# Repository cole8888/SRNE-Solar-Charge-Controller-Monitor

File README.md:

# SRNE-Solar-Charge-Controller-Monitor

Read data from SRNE solar charge controllers via modbus over RS232.

This repository contains several example programs for reading data from SRNE solar charge controllers using Raspberry Pi, ESP32, ESP8266 and Arduino Nano / Uno.

Based on the modbus manuals, this should also work with some Renogy controllers, but I don't have one to test with. Also, verify the wiring is compatible with your controller.

<hr>

## Example Setups:

Here are some example programs to get started. If you follow the setup instructions in the readme files of each directory, you should be able to talk to your controller. If you are just getting started, don't use the MQTT ones.

### [Raspberry Pi](./RaspberryPi-Examples/)

### [ESP32](./ESP32-Examples/)

### [ESP8266](./ESP8266-Examples/)

### [Arduino Nano / Uno](./Arduino-Example/)

<hr>

## Web-Interface and MQTT

I've included an [example web interface](./Web-Interface-Example/) you can use in combination with the MQTT-enabled example programs. To use it, you will need to setup an MQTT broker such as [Mosquitto](https://github.com/eclipse/mosquitto) or use a cloud broker. You will also need to set all the appropriate settings in the chosen program and the [index.js](./Web-Interface-Example/index.js) file.

I also included my [custom web interface](./My-Current-Setup/Web-Interface/) which I am using for my setup. It has the ability to read data from and control smart plugs flashed with Tasmota.

<hr>

## My Current Setup:

The setup I use is a customized version of the ESP32 Example, I also designed a custom PCB. Have a look at [My-Current-Setup](./My-Current-Setup) if you want some inspiration for your own setup!

<hr>

## Troubleshooting:

If you notice lots of timeouts, or other errors, try some these steps before creating an issue:

- Try a different power supply and USB cable. My ML2440 does not respond when I use one of my USB power bricks, but it does with another.
- Try increasing the modbus timeout value.
- Try using a shorter cables and moving them away from interference.
- Verify you are using straight cables and not ones that reverse from one end to the other.
- Try using HardwareSerial instead of SoftwareSerial. I've found HardwareSerial is more reliable, configure the program to use it if you are having problems.

<b>If these don't help or if you need clarification, feel free to create an issue and I'll see what I can do!</b>

<hr>

## Other notes:

- I've included the [SRNE modbus manual](./SRNE-MODBUS.pdf) if you want to have a look at it. My examples read all the registers I think are important, but there are lots of other registers which I haven't touched. Be careful, some of them can be written to!

- The Python version was originally based on: http://vcsco.com/uncategorized/renogy-rover-monitoring-with-the-raspberry-pi/

- The Web-Interface was originally based on: https://github.com/fabaff/mqtt-panel

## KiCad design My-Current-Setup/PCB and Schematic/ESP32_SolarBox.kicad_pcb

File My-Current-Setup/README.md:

# My-Current-Setup

This is the setup I currently use. Feel free to use it for inspiration!

This version isn't intended to be plug and play like the other examples as it is specific to my needs.

## Layout

I have 3 solar charge controllers, one for the front, side, and back arrays. They feed into the ESP32 which collects the data and publishes it to an MQTT server that clients (such as the web-ui) can connect to.

I also have an ESP8266 with an LCD attached that subscribes to the MQTT feed to display some data in a convenient location around the house.

## Libraries

The libraries this project uses are:

- https://github.com/4-20ma/ModbusMaster
- https://github.com/bblanchon/ArduinoJson
- https://github.com/knolleary/pubsubclient
- https://github.com/plerup/espsoftwareserial/ (Optional, needed for >2 controllers)
- https://github.com/ayushsharma82/AsyncElegantOTA (Optional, Over the air updates)
- https://github.com/ayushsharma82/WebSerial (Optional, Over the air debugging)
- https://github.com/me-no-dev/ESPAsyncWebServer/ (Dependency of OTA and WebSerial)
- https://github.com/me-no-dev/AsyncTCP/ (Dependency of OTA and WebSerial)
- https://github.com/fdebrabander/Arduino-LiquidCrystal-I2C-library (Optional, for receiver)

## Hardware

### PCB

I designed a custom PCB for this, have a look at the [PCB files and schematic](./PCB%20and%20Schematic/).

Each PCB can handle up to 6 charge controllers at once!

NOTE: If you do plan to use my PCB, make sure you verify the footprint of the ESP32 you plan to use. The ones I have are a bit narrower than most, so you may need to adjust the footprint.

### Components:

This list is for a fully populated PCB, you may not need everything here, see schematic for details.

- 1 x [ESP32 DevKit Narrow](https://www.amazon.ca/gp/product/B07QCP2451/) (Unless you adjusted the PCB footprint yourself)
- 3 x [MAX3232](https://www.digikey.ca/en/products/detail/analog-devices-inc-maxim-integrated/MAX3232EEPE/1512691) (Or equivalent)
- 3 x [10uF Capacitor](https://www.digikey.ca/en/products/detail/nichicon/ULD2A100MED1TD/7365013)
- 9 x [0.47uF Capacitor](https://www.digikey.ca/en/products/detail/tdk-corporation/FG28X7R1H474KRT06/5803214)
- 3 x [0.1uF Capacitor](https://www.digikey.ca/en/products/detail/vishay-beyschlag-draloric-bc-components/K104K15X7RF5TL2/286538)
- 6 x [1kOhm Resistor](https://www.digikey.ca/en/products/detail/stackpole-electronics-inc/CF14JT1K00/1741314)
- 6 x [6P6C Jack](https://www.digikey.ca/en/products/detail/amphenol-cs-commercial-products/RJE031660110/4889694)
- 6 x [6P6C Straight Cable](https://www.digikey.ca/en/products/detail/assmann-wsw-components/AT-S-26-6-6-B-7-R/1972588)
- 2 x [1000uF Capacitor](https://www.digikey.ca/en/products/detail/rubycon/35ZLH1000MEFC12-5X20/3564067) (Recommended)
- 2 x [19 Position Female Header](https://www.digikey.ca/en/products/detail/sullins-connector-solutions/PPTC191LFBN-RC/810157) (Recommended, for ESP32)
- 3 x [16 Pin Dip Socket](https://www.digikey.ca/en/products/detail/amphenol-cs-fci/DILB16P-223TLF/4292068) (Recommended, for MAX3232)
- 1 x [3 position screw terminal](https://www.digikey.ca/en/products/detail/phoenix-contact/1984620/950850) (Optional)

## Web Interface

This is a customized version of the [example web interface](../Web-Interface-Example/). It has a different layout since I needed to display data from 3 charge controllers while also having smart plug controls.

<hr>

- The Web interface was originally based on https://github.com/fabaff/mqtt-panel
- Server icon in diagram is from [Roundicons](https://www.flaticon.com/free-icons/server).

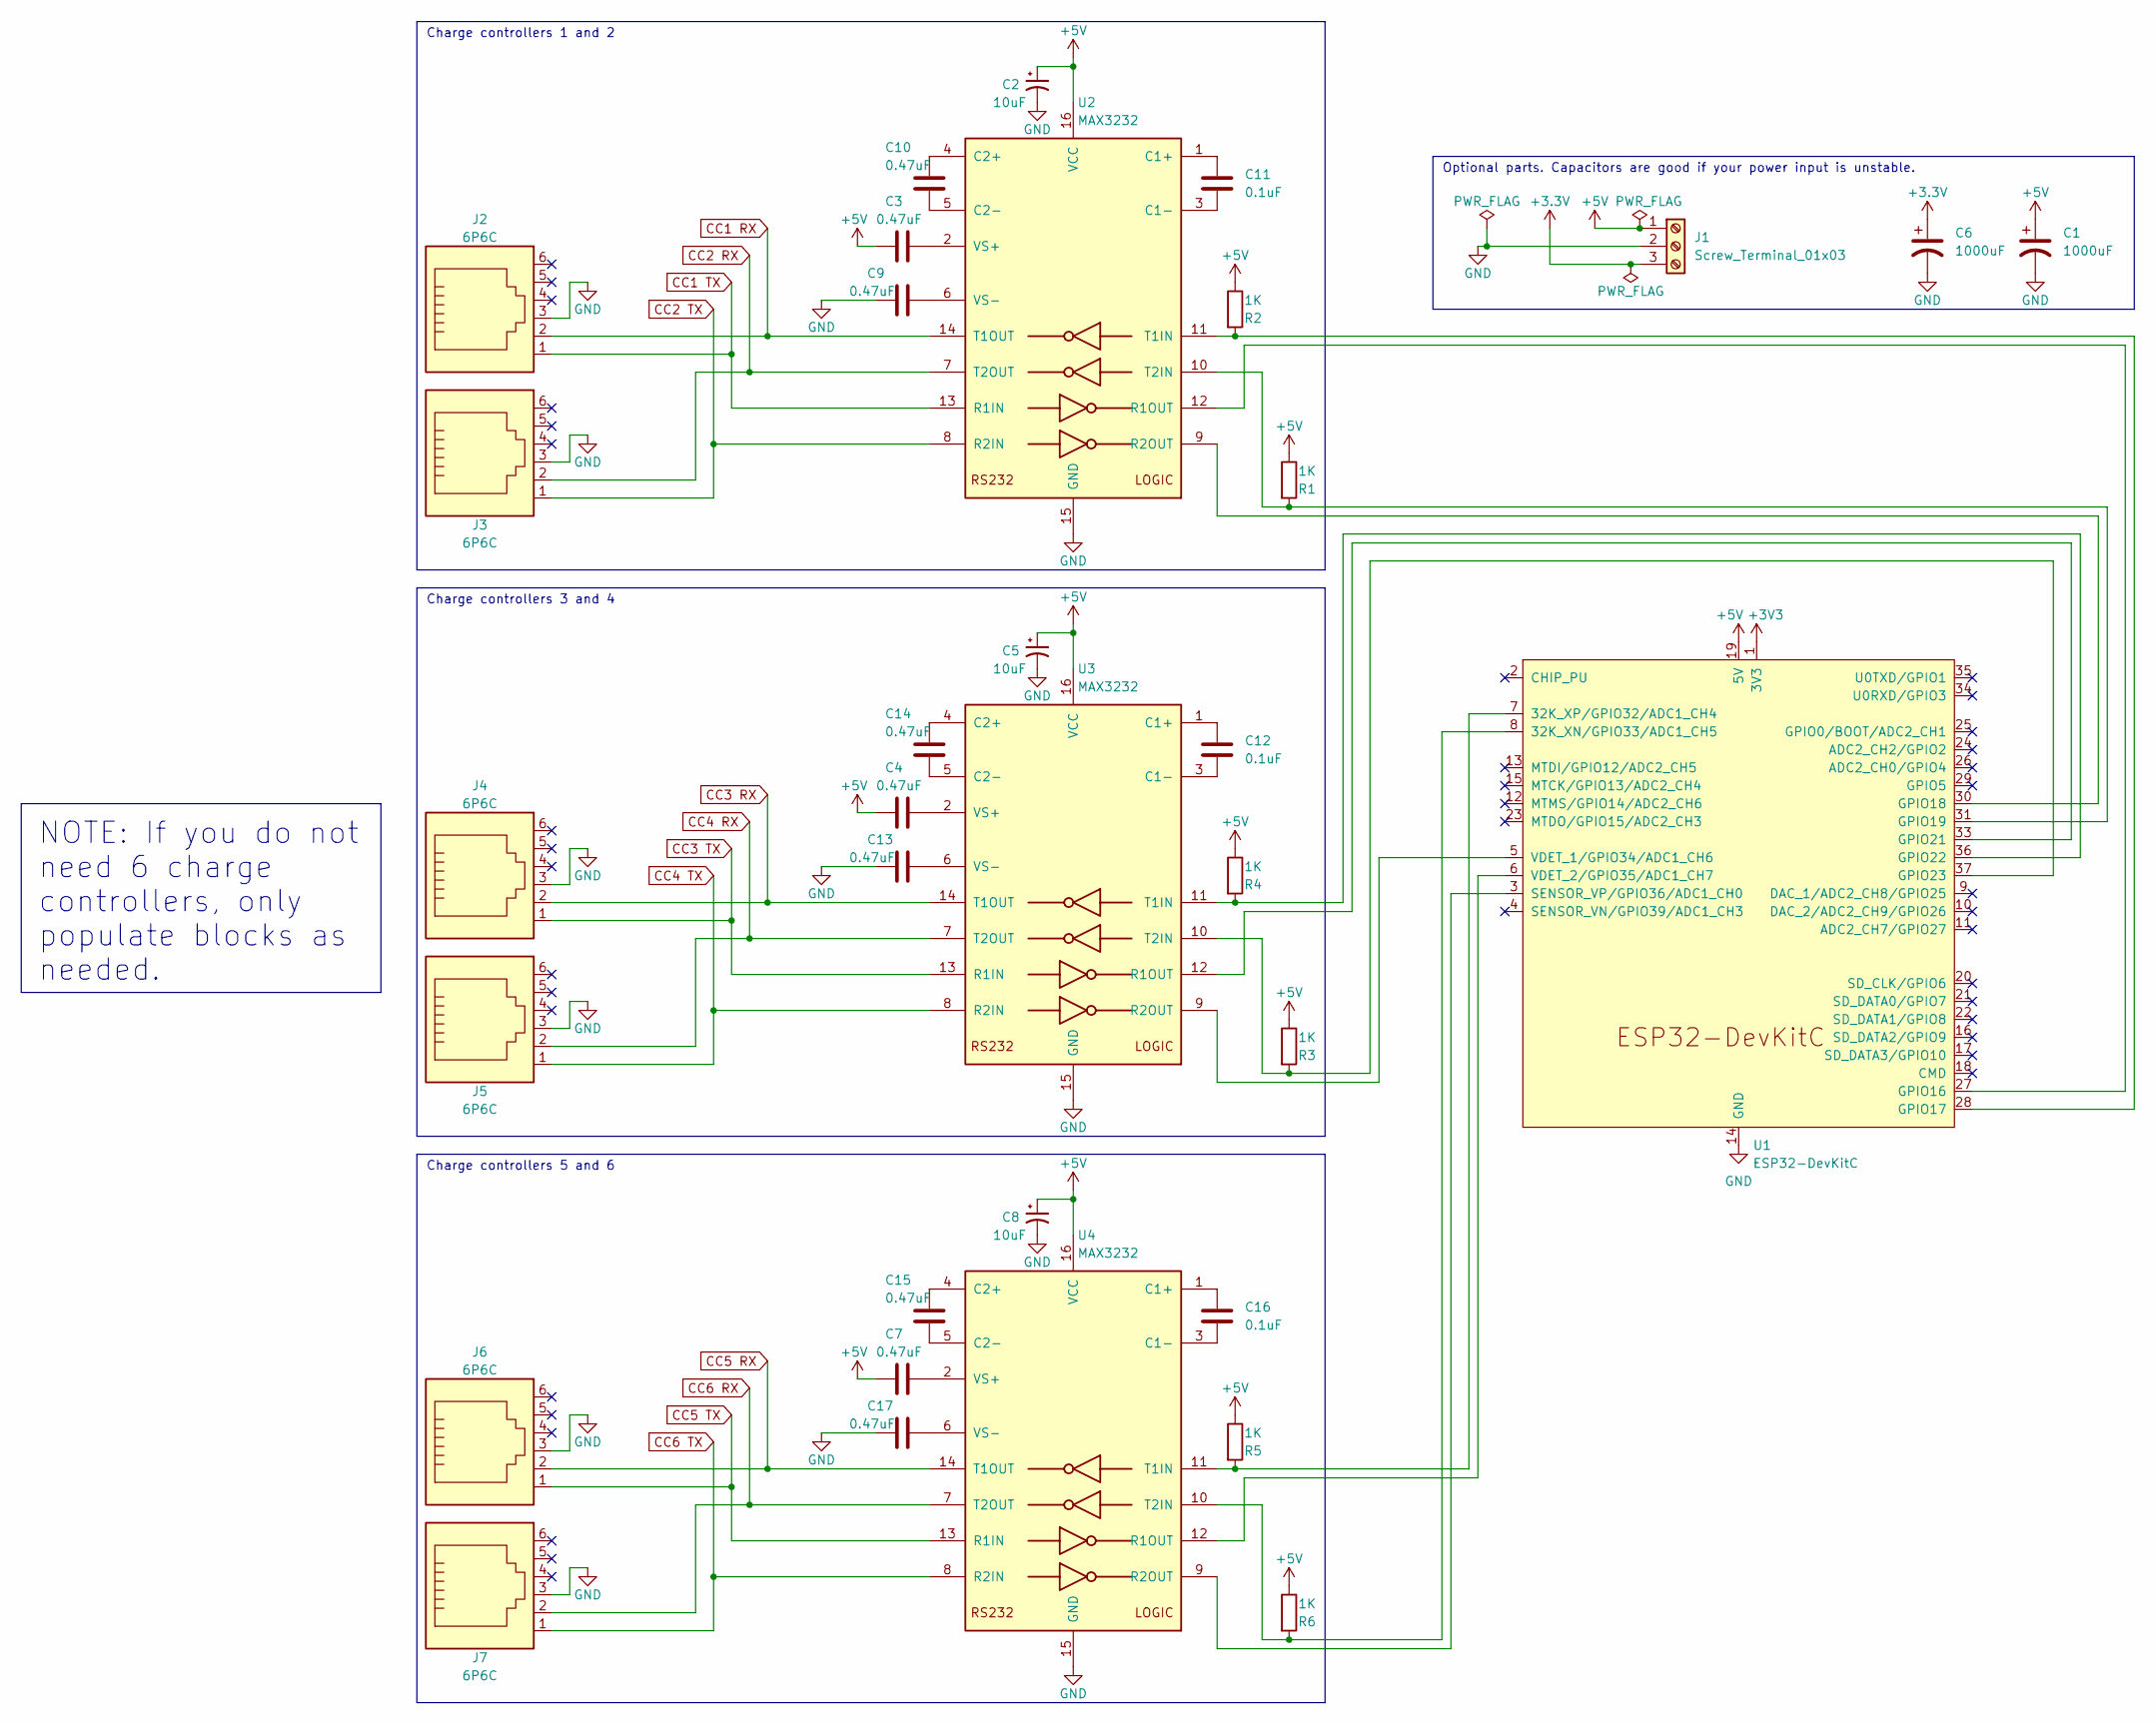
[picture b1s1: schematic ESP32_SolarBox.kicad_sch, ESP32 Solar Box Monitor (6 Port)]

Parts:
C1, C6: 1000uF; CP_Radial_D12.5mm_P5.00mm
C2, C5, C8: 10uF; CP_Radial_D6.3mm_P2.50mm
C3, C4, C7, C9, C10, C13, C14, C15, C17: 0.47uF; C_Disc_D4.7mm_W2.5mm_P5.00mm
C11, C12, C16: 0.1uF; C_Disc_D5.0mm_W2.5mm_P2.50mm
J1: Screw_Terminal_01x03; TerminalBlock_Phoenix_PT-1,5-3-3.5-H_1x03_P3.50mm_Horizontal
J2, J3, J4, J5, J6, J7: 6P6C; RJ12_Amphenol_54601
R1, R2, R3, R4, R5, R6: 1K; R_Axial_DIN0207_L6.3mm_D2.5mm_P10.16mm_Horizontal
U1: ESP32-DevKitC
U2, U3, U4: MAX3232; DIP-16_W7.62mm

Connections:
+5V: C1.1, C2.1, C3.2, C4.2, C5.1, C7.2, C8.1, J1.1, R1.1, R2.1, R3.1, R4.1, R5.1, R6.1, U1.19 (5V), U2.16 (VCC), U3.16 (VCC), U4.16 (VCC)
CC1 RX: J2.2, U2.14 (T1OUT)
CC1 TX: J2.1, U2.13 (R1IN)
CC2 RX: J3.2, U2.7 (T2OUT)
CC2 TX: J3.1, U2.8 (R2IN)
CC3 RX: J4.2, U3.14 (T1OUT)
CC3 TX: J4.1, U3.13 (R1IN)
CC4 RX: J5.2, U3.7 (T2OUT)
CC4 TX: J5.1, U3.8 (R2IN)
CC5 RX: J6.2, U4.14 (T1OUT)
CC5 TX: J6.1, U4.13 (R1IN)
CC6 RX: J7.2, U4.7 (T2OUT)
CC6 TX: J7.1, U4.8 (R2IN)
GND: C1.2, C2.2, C5.2, C6.2, C8.2, C9.2, C13.2, C17.2, J1.2, J2.3, J3.3, J4.3, J5.3, J6.3, J7.3, U1.14 (GND), U1.32 (GND), U1.38 (GND), U2.15 (GND), U3.15 (GND), U4.15 (GND)
unnamed: R6.2, U1.8 (32K_XN/GPIO33/ADC1_CH5), U4.10 (T2IN)
unnamed: R5.2, U1.7 (32K_XP/GPIO32/ADC1_CH4), U4.11 (T1IN)
unnamed: U1.27 (GPIO16), U2.12 (R1OUT)
unnamed: R2.2, U1.28 (GPIO17), U2.11 (T1IN)
unnamed: U1.30 (GPIO18), U2.9 (R2OUT)
unnamed: R1.2, U1.31 (GPIO19), U2.10 (T2IN)
unnamed: U1.33 (GPIO21), U3.12 (R1OUT)
unnamed: R4.2, U1.36 (GPIO22), U3.11 (T1IN)
unnamed: R3.2, U1.37 (GPIO23), U3.10 (T2IN)
unnamed: U1.3 (SENSOR_VP/GPIO36/ADC1_CH0), U4.9 (R2OUT)
unnamed: U1.5 (VDET_1/GPIO34/ADC1_CH6), U3.9 (R2OUT)
unnamed: U1.6 (VDET_2/GPIO35/ADC1_CH7), U4.12 (R1OUT)
unnamed: C11.1, U2.1 (C1+)
unnamed: C11.2, U2.3 (C1-)
unnamed: C10.1, U2.4 (C2+)
unnamed: C10.2, U2.5 (C2-)
unnamed: C3.1, U2.2 (VS+)
unnamed: C9.1, U2.6 (VS-)
unnamed: C12.1, U3.1 (C1+)
unnamed: C12.2, U3.3 (C1-)
unnamed: C14.1, U3.4 (C2+)
unnamed: C14.2, U3.5 (C2-)
unnamed: C4.1, U3.2 (VS+)
unnamed: C13.1, U3.6 (VS-)
unnamed: C16.1, U4.1 (C1+)
unnamed: C16.2, U4.3 (C1-)
unnamed: C15.1, U4.4 (C2+)
unnamed: C15.2, U4.5 (C2-)
unnamed: C7.1, U4.2 (VS+)
unnamed: C17.1, U4.6 (VS-)

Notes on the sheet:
NOTE: If you do not need 6 charge controllers, only populate blocks as needed.
Charge controllers 3 and 4
Charge controllers 5 and 6
Optional parts. Capacitors are good if your power input is unstable.
Charge controllers 1 and 2

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
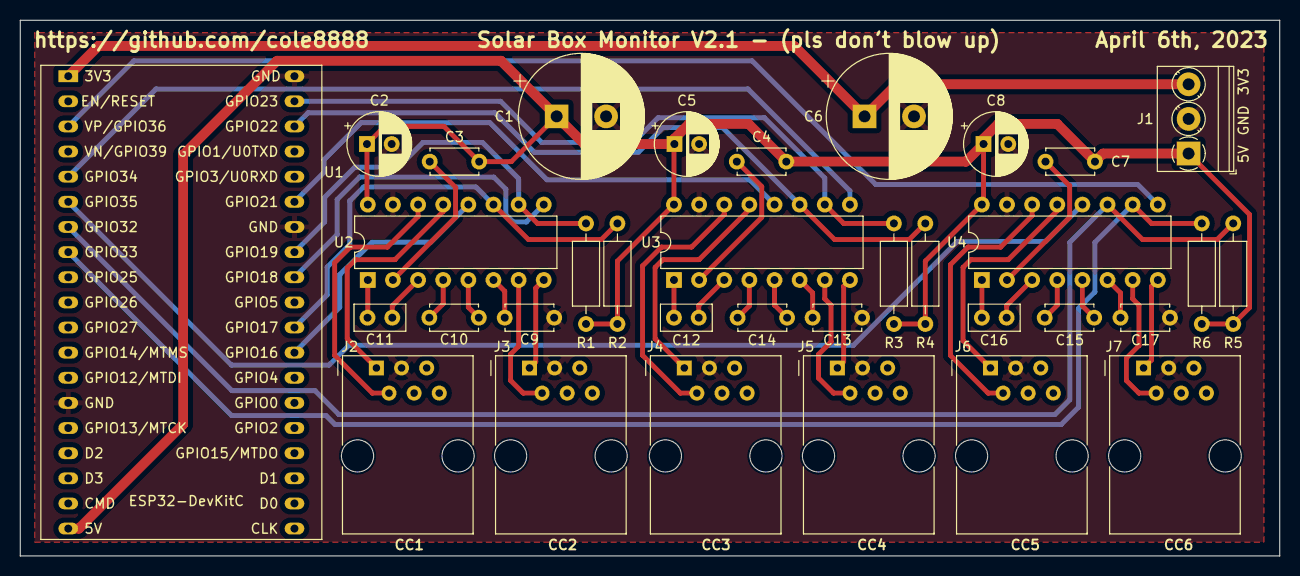
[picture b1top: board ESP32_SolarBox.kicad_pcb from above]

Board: 2 copper layers, 127.3 x 54.1 mm, 34 parts (0 on the bottom side), 45 nets.

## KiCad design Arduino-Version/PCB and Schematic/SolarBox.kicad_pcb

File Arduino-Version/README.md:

# Arduino Version
This is the version I've worked the most on and is the one I use for my setup. I've included a couple of example arduino sketches and schematics so you can get started easily. I've also included a copy of the setup I currently use, I'll explain it more at the end.

## Setup
Depending on the device you want to use, the connections will be a bit different, a few things will remain the same though. I have created schematics for the Arduino Nano and the ESP8266 examples.

### Libraries
The libraries this project uses are:
- https://github.com/smarmengol/Modbus-Master-Slave-for-Arduino (**2 LINES MUST BE MODIFIED!**)
- https://github.com/nRF24/RF24 (Only for multiple controllers)
- https://github.com/nRF24/RF24Network (Only for multiple controllers)
- https://github.com/knolleary/pubsubclient (Only in my setup)
- https://github.com/fdebrabander/Arduino-LiquidCrystal-I2C-library (Only in my setup)
- https://github.com/Zanduino/BME680 (Only in my setup)
- https://github.com/adafruit/Adafruit_ADS1X15 (Only in my setup)

#### Modbus library modifications
The charge controllers will always respond to address 255. This is handy since some charge controllers appear to be using unknown addresses. Unfortunately the library I am using for modbus does not support addresses above 247, so we need to make two small changes to it.

Open the your arduino libraries folder and open the `Modbus-Master-Slave-for-Arduino-master` folder, then `ModbusRtu.h`.
Search for `247` and you should find these two sections:

In each section change the `247` to `255`. Save and restart your Arduino IDE.

If you already know the address of your charge controller (it is probably `1`) you do not need to make these changes to the library and you should update the `MODBUS_SLAVE_ADDR` constant in the Arduino sketch with the appropriate address.

### Charge controller pinout
Here is the pinout of the 6P6C connector on the charge controller as indicated by the modbus manual from SRNE.

### Charge controller cable to MAX3232
Here is how I connect the charge controller to the MAX3232 breakout board. I used a male DB9 connector to plug into the breakout board and to connect it to the brad board, only the top row of contacts are used. My cable's wire colors may not match yours, check out [6P6C-Connector.jpg](./6P6C-Connector.jpg) to compare yours against mine. (Note that the wire colors do not match their stereotypical roles. Blame whoever came up with the charge controller pinout)

### MAX3232 Voltage
One thing to note is that the MAX3232 can be powered by 5V or 3.3V, so you might see them used interchangeably in the pictures.

## Arduino Nano

## ESP8266

If you use the ESP8266 make sure you adjust the RX and TX pins for the software serial in the program. According to these pictures, the new values would be `MAX3232_RX = D1` and `MAX3232_TX = D2`.

## Multiple Charge Controllers
You may want to use multiple charge controllers, in which case I would suggest having a look at the multiple charge controllers example. When using multiple charge controllers I would recommend splitting up the roles between the Arduinos and having multiple transmitters and a single receiver.

## My current setup

This is the version I currently use for my solar system.
As such, this version isn't really intended to be immediately plug and play. While the transmitter code is not too different, the receiver is quite specific to my application.

I use three charge controllers. There are panels on the front of the house (CC1), side (CC2), and back (CC3). Each charge controller has an Arduino nano attached to it and there is an additional arduino for reporting some miscellaneous sensor readings. The Arduinos send the information back to a receiver node (ESP8266) using RF24 modules. The transmitter then publishes the data over MQTT to a server which hosts it on a web interface. I've also included the PCB I'm using.

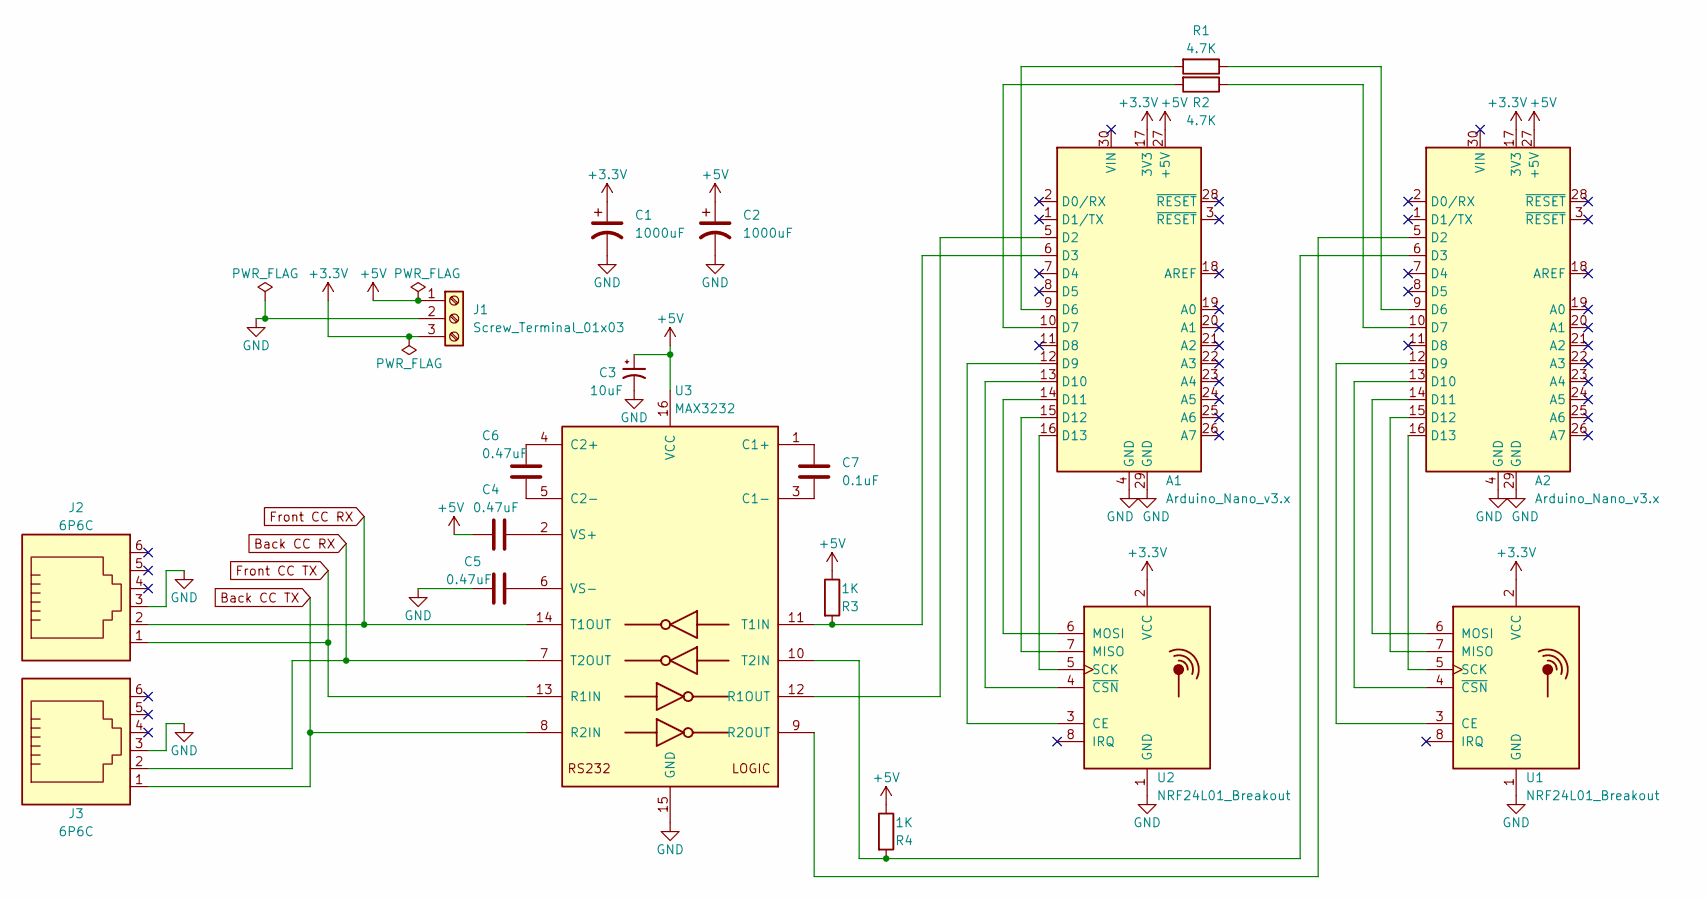
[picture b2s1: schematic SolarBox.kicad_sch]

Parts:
A1, A2: Arduino_Nano_v3.x; Arduino_Nano
C1, C2: 1000uF; CP_Radial_D12.5mm_P5.00mm
C3: 10uF; CP_Radial_D6.3mm_P2.50mm
C4, C5, C6: 0.47uF; C_Disc_D4.7mm_W2.5mm_P5.00mm
C7: 0.1uF; C_Disc_D5.0mm_W2.5mm_P2.50mm
J1: Screw_Terminal_01x03; TerminalBlock_Phoenix_PT-1,5-3-3.5-H_1x03_P3.50mm_Horizontal
J2, J3: 6P6C; RJ12_Amphenol_54601
R1, R2: 4.7K; R_Axial_DIN0309_L9.0mm_D3.2mm_P12.70mm_Horizontal
R3, R4: 1K; R_Axial_DIN0309_L9.0mm_D3.2mm_P12.70mm_Horizontal
U1, U2: NRF24L01_Breakout; nRF24L01_Breakout
U3: MAX3232; DIP-16_W7.62mm

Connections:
+3V3: A1.17 (3V3), A2.17 (3V3), C1.1, J1.3, U1.2 (VCC), U2.2 (VCC)
+5V: A1.27 (+5V), A2.27 (+5V), C2.1, C3.1, C4.2, J1.1, R3.1, R4.1, U3.16 (VCC)
Back CC RX: J3.2, U3.7 (T2OUT)
Back CC TX: J3.1, U3.8 (R2IN)
Front CC RX: J2.2, U3.14 (T1OUT)
Front CC TX: J2.1, U3.13 (R1IN)
GND: A1.4 (GND), A1.29 (GND), A2.4 (GND), A2.29 (GND), C1.2, C2.2, C3.2, C5.2, J1.2, J2.3, J3.3, U1.1 (GND), U2.1 (GND), U3.15 (GND)
unnamed: A1.5 (D2), U3.12 (R1OUT)
unnamed: A1.6 (D3), R3.2, U3.11 (T1IN)
unnamed: A1.9 (D6), R1.2
unnamed: A1.10 (D7), R2.2
unnamed: A1.12 (D9), U2.3 (CE)
unnamed: A1.13 (D10), U2.4 (~CSN)
unnamed: A1.14 (D11), U2.6 (MOSI)
unnamed: A1.15 (D12), U2.7 (MISO)
unnamed: A1.16 (D13), U2.5 (SCK)
unnamed: A2.5 (D2), U3.9 (R2OUT)
unnamed: A2.6 (D3), R4.2, U3.10 (T2IN)
unnamed: A2.9 (D6), R1.1
unnamed: A2.10 (D7), R2.1
unnamed: A2.12 (D9), U1.3 (CE)
unnamed: A2.13 (D10), U1.4 (~CSN)
unnamed: A2.14 (D11), U1.6 (MOSI)
unnamed: A2.15 (D12), U1.7 (MISO)
unnamed: A2.16 (D13), U1.5 (SCK)
unnamed: C4.1, U3.2 (VS+)
unnamed: C5.1, U3.6 (VS-)
unnamed: C6.1, U3.4 (C2+)
unnamed: C6.2, U3.5 (C2-)
unnamed: C7.1, U3.1 (C1+)
unnamed: C7.2, U3.3 (C1-)

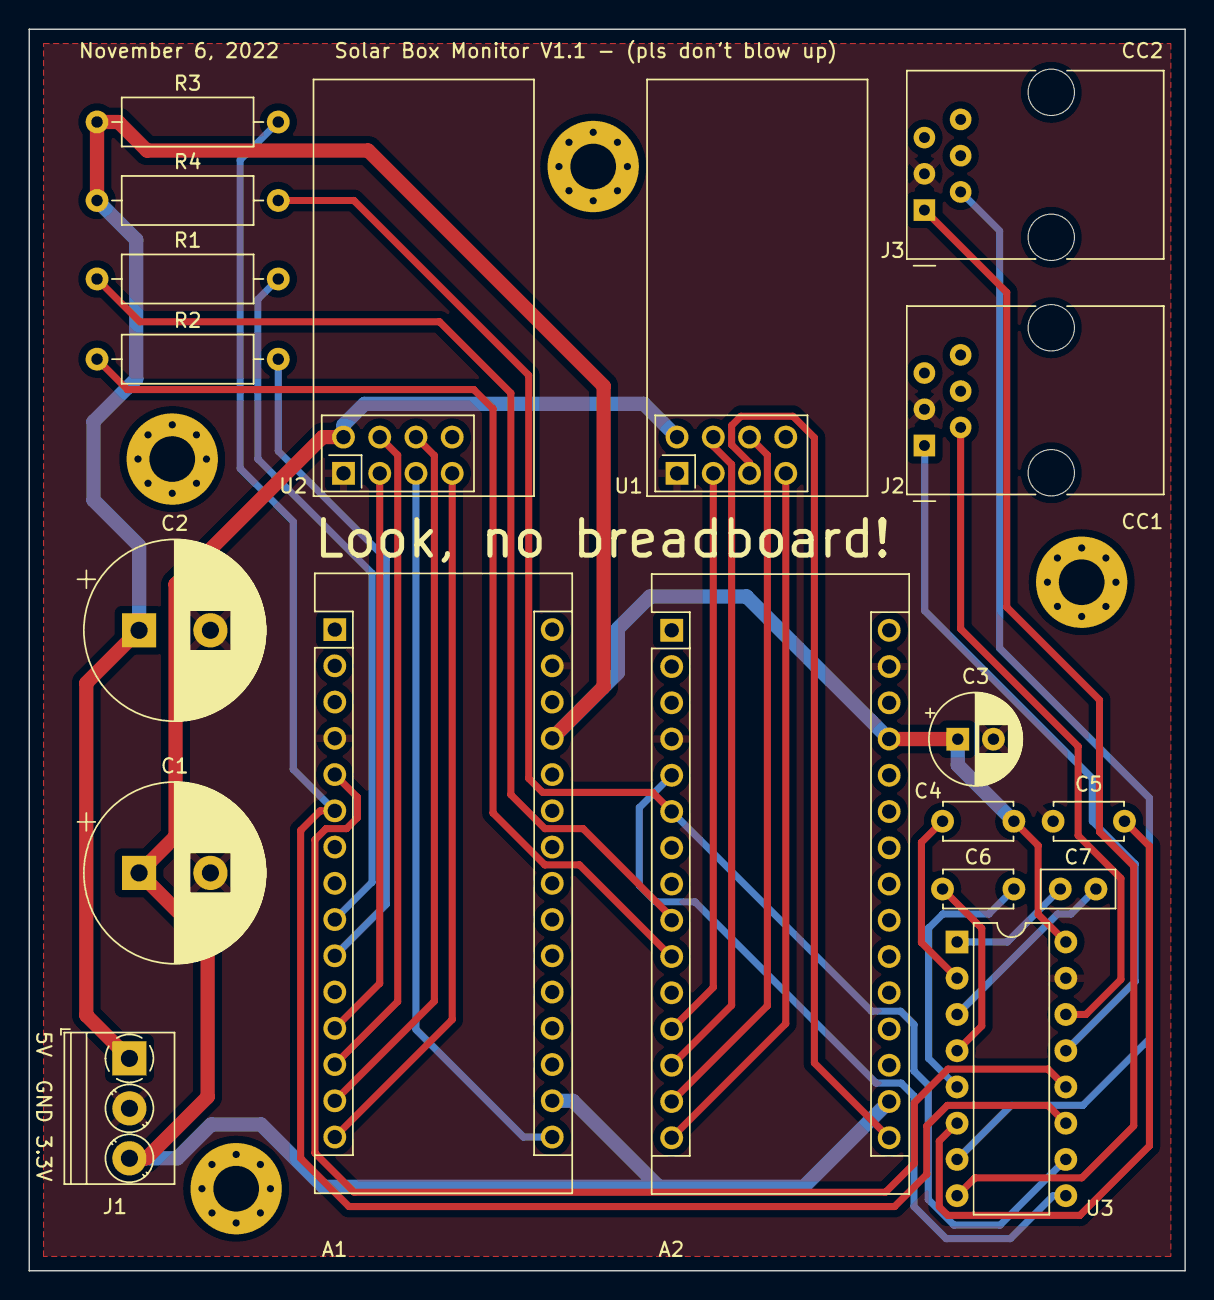
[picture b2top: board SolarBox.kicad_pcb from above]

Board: 2 copper layers, 81.0 x 87.0 mm, 19 parts (0 on the bottom side), 31 nets.

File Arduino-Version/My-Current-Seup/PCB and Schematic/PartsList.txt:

2x Arduino Nano (https://www.amazon.ca/gp/product/B0816SGKHH)
2x RF24 Module (https://www.amazon.ca/Arduino-NRF24L01-2-4GHz-Wireless-Trans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
1x MAX3232 (https://www.digikey.ca/en/products/detail/analog-devices-inc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
2x 6P6C Jack (https://www.digikey.ca/en/products/detail/adam-tech/MTJ-66GX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
2x 6P6C Cable (https://www.digikey.ca/en/products/detail/assmann-wsw-compon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
1x 0.1uF Capacitor (https://www.digikey.ca/en/products/detail/vishay-beyschlag-d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
3x 0.47uF Capacitor (https://www.digikey.ca/en/products/detail/tdk-corporation/FG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
1x 10uF Capacitor (https://www.digikey.ca/en/products/detail/nichicon/ULD2A100M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
2x 1000uF Capacitor (https://www.digikey.ca/en/products/detail/rubycon/35ZLH1000M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
2x 1K Resistor (https://www.digikey.ca/en/products/detail/stackpole-electron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
2x 4.7K Resistor (https://www.digikey.ca/en/products/detail/stackpole-electron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
1x Screw Terminal Block [Optional] (https://www.digikey.ca/en/products/detail/phoenix-contact/19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

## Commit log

2021-06-22 Fix fault detection
    Was reading wrong register for controller faults. Need to read 0x0122 (290) and not 0x0121 (289). Had no way of testing this until recently I got a panel overvoltage fault by accident. Also the wrong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
2021-07-03 Fix incorrect comment.
    Accidentally placed the wrong comments on the publish statements for the battery and controller temperatures.
2021-07-07 Fix inconsistent MQTT topic name.
    This was a typo I discovered while writing a web interface to view the MQTT data.
2021-07-25 Create SolarMonitor.py
    Updated version with stuff cleaned up a bit. I no longer send strings for fault detection, I just send the raw charge controller data and let the client parse it.
2022-05-11 Fix issue with high VOC values for arduino version and added fault data to raspberry pi version.
2022-10-08 Remove unused commented code, fix typo.
2022-11-20 Add CC3, add PCB and schematic.
2022-11-20 Fix headings and add PCB image
2022-11-20 Fix readme image not loading
2022-11-21 More detailed documentation for Arduino. Upload examples for Arduino. Upload schematics and pictures for single charge controller examples. Fix incorrect index in python version. Fix incorrect regist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
2022-11-21 Fix readme images.
2022-11-21 Fix readme images
2022-11-21 Fix readme images (again)
2022-12-09 test address fix
2022-12-09 add modified modbus library.
2022-12-09 Add updated modbus manual from SRNE
2022-12-24 - switch cc address to 255 - add instructions for how to modify the modbus library to handle 255 - fix bug in my current setup where if mqtt server died LCD would refresh slowly since MQTT kept tryin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
2022-12-24 add request delay jitter to my current setup
2022-12-24 - fix inconsistencies in formatting between files - update readme files
2023-04-23 Add v2,1 (ESP32). Still need to do testing of some changes.
2023-04-23 fix spelling and readmes.
2023-04-28 - Add web interfaces. - Remove old arduino stuff. - Move stuff around to make it easier to navigate. - Fix problem with python version that didn't let it run at all. - Add MQTT example programs (unte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
2023-05-01 Finishing touches.
2023-05-01 Fix broken links and grammar.
2023-05-06 Fix modal X button not unlocking plug.
2023-05-06 update date.
2023-05-09 Add 4 new smart plugs.
2023-05-17 Use HW serial for CC1. Remove redundant str call in python.
2023-05-17 Remove unused item in example interface element id list.
